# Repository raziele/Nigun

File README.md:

## Nigun (Melody)
RF down-converter for (but not only for) SDR

## PURPOSE
Allow low-frequency SDR (mainly RTL-SDR) to recieve wireless signals in frequencies higher than 1500MHz
Nigun is platform-independant, so it can be paired with other devices such as YARD stick ONE and PandwaRF too!

## MAIN PROPERTIES
* Dynamic LO - LO will be determined by the user and programmed by the MCU
* Almost no filtering - will leave this challenge outside of this project scope
* Power up and programming via micro-usb connector. Should be able to power up from a USB power-pack (but probably not from a computer port)
* Highest RF frequency will be 3GHz
* Product also features a VCO for signal-generation purposes. VCO support should be 200-2700MHz

## DESIGN DETAILS
Can be found currently on http://slides.com/raziele/software-define-radio-4-5-6-7-8#/
All details should be updated here in the near future

## CURRENT STATUS
2017-05: Finished PCB design. Working on some finishing but I should order first batch during June

## CREDITS
* All those who were patient enough to teach, review, and answer my endless questions
* Michele Perla and his HACK project - for the Atmel SAMD21E reference design

## LICENSE
I haven't dealt with the licensing part yet, though it will probably be under CERN OHL v. 1.2.
For now, please contact me for any licensing request.

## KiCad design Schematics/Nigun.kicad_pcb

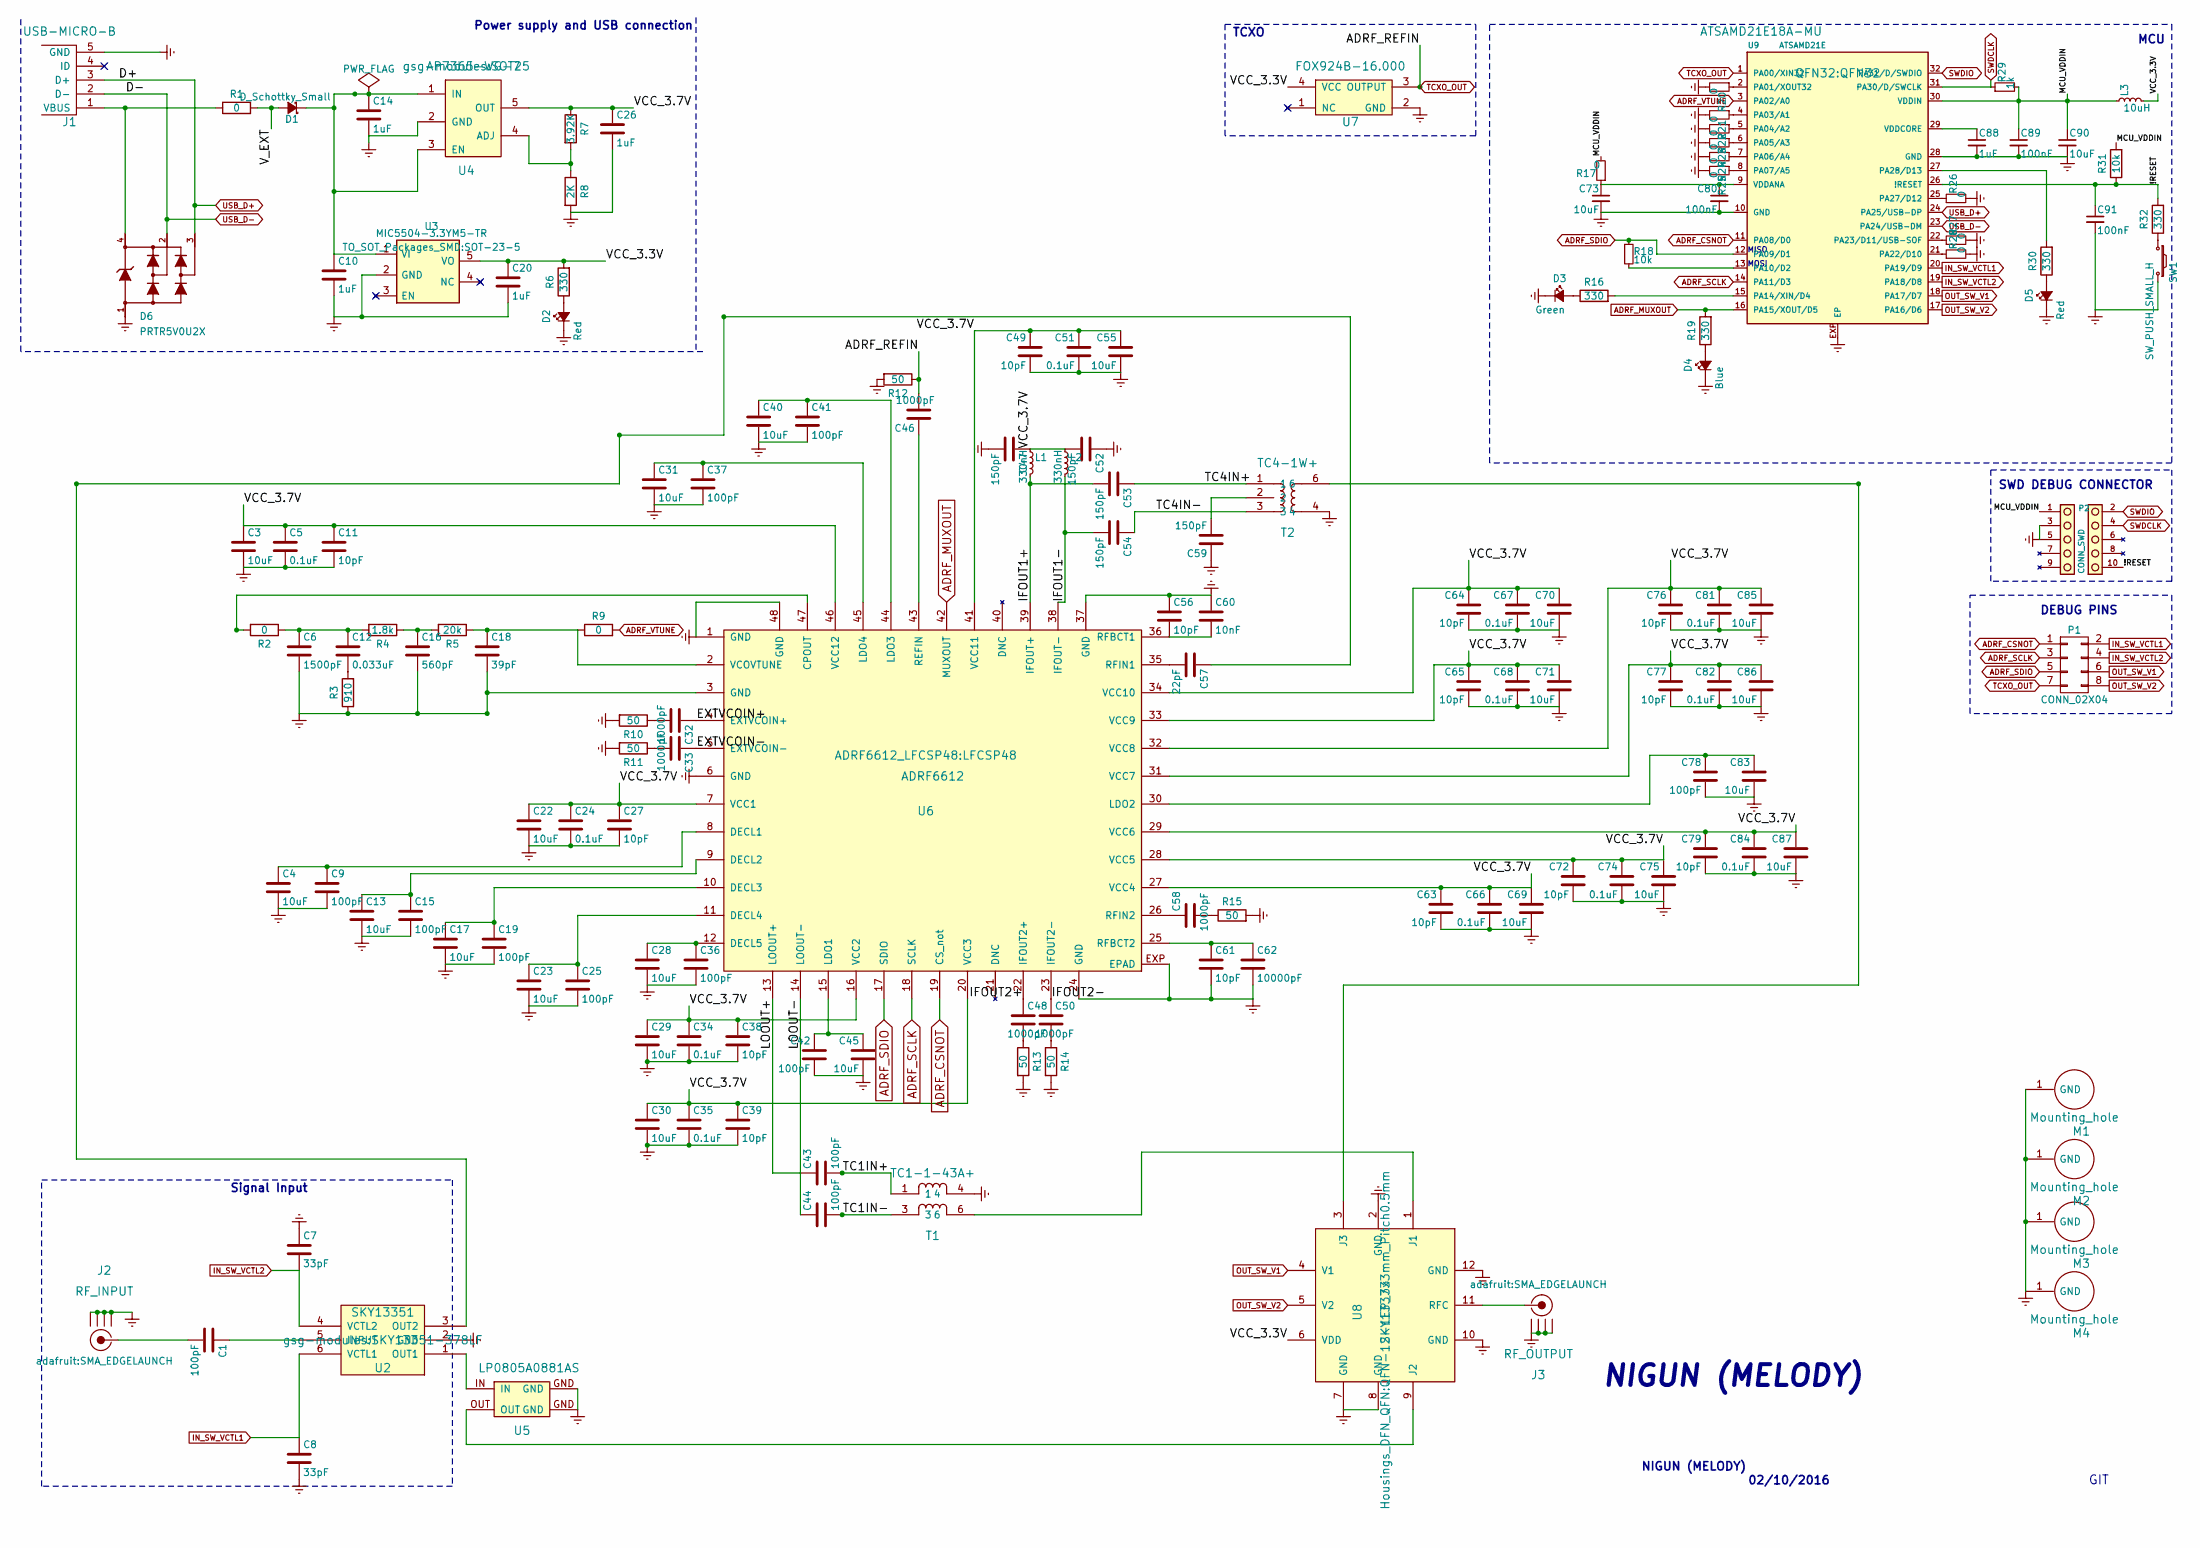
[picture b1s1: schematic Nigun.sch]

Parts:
C1, C9, C15, C19, C25, C36, C37, C41, C42, C43, C44, C78: 100pF; C_0402
C3, C4, C13, C17, C22, C23, C28, C29, C30, C31, C40, C45, C55, C69, C70, C71, C73, C75, C83, C85, C86, C87, C90: 10uF; C_0402
C5, C24, C34, C35, C51, C66, C67, C68, C74, C81, C82, C84: 0.1uF; C_0402
C6: 1500pF; C_0402
C7, C8: 33pF; C_0402
C10, C14, C20, C26, C88: 1uF; C_0402
C11, C27, C38, C39, C49, C56, C61, C63, C64, C65, C72, C76, C77, C79: 10pF; C_0402
C12: 0.033uF; C_0402
C16: 560pF; C_0402
C18: 39pF; C_0402
C32, C33, C46, C48, C50, C58: 1000pF; C_0402
C47, C52, C53, C54, C59: 150pF; C_0402
C57: 22pF; C_0402
C60: 10nF; C_0402
C62: 10000pF; C_0402
C80, C89, C91: 100nF; C_0402
D1: D_Schottky_Small; DO-214AA-SMB
D2, D5: Red; LED_kingsbright
D3: Green; LED_kingsbright
D4: Blue; LED_kingsbright
D6: PRTR5V0U2X; SOT143B
J1: USB-MICRO-B; FRAMATOME_10118194-0001LF
J2: RF_INPUT; SMA_EDGELAUNCH
J3: RF_OUTPUT; SMA_EDGELAUNCH
L1, L2: 330nH; C_0402
L3: 10uH; C_0603_HandSoldering
M1, M2, M3, M4: Mounting_hole; Mounting_hole_100mil
P1: CONN_02X04; HEADER-2x4
P2: CONN_SWD; HEADER-2x5
R1, R2, R9, R17, R20, R21, R22, R23, R24, R25, R26, R27, R28: 0; R_0402
R3: 910; R_0402
R4: 1.8k; R_0402
R5: 20k; R_0402
R6, R16, R19, R30, R32: 330; R_0402
R7: 3.92K; R_0402
R8: 2K; R_0402
R10, R11, R12, R13, R14, R15: 50; R_0402
R18, R31: 10k; R_0402
R29: 1k; R_0402
SW1: SW_PUSH_SMALL_H; Tactile_SW
T1: TC1-1-43A+; AT224-1A
T2: TC4-1W+; AT224-1A
U2: SKY13351; SKY13351-378LF
U3: MIC5504-3.3YM5-TR; SOT-23-5
U4: AP7365-WG-7; SOT25
U5: LP0805A0881AS; CP_0805
U6: ADRF6612; LFCSP48
U7: FOX924B-16.000; FOX924
U8: SKY13373; QFN-12-1EP_3x3mm_Pitch0.5mm
U9: ATSAMD21E; QFN32

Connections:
/!RESET: C91.1, P2.10 (nRESET), R31.1, R32.2, U9.26 (!RESET)
/EXTVCOIN+: C32.1, U6.4 (EXTVCOIN+)
/EXTVCOIN-: C33.1, U6.5 (EXTVCOIN-)
/IFOUT1+: C53.2, L1.2, U6.39 (IFOUT+)
/IFOUT1-: C54.2, L2.2, U6.38 (IFOUT-)
/IFOUT2+: C48.1, U6.22 (IFOUT2+)
/IFOUT2-: C50.1, U6.23 (IFOUT2-)
/LOOUT+: C43.1, U6.13 (LOOUT+)
/LOOUT-: C44.1, U6.14 (LOOUT-)
/MCU_VDDIN: C89.1, C90.1, L3.1, P2.1 (VTref), R17.2, R29.2, R31.2, U9.30 (VDDIN)
/TC1IN+: C43.2, T1.1
/TC1IN-: C44.2, T1.3
/TC4IN+: C53.1, T2.1
/TC4IN-: C54.1, T2.3
/VCC_3.3V: C20.1, L3.2, R6.2, U3.5 (VO), U7.4 (VCC), U8.6 (VDD)
/VCC_3.7V: C3.1, C5.1, C11.1, C22.1, C24.1, C26.1, C27.1, C29.1, C30.1, C34.1, C35.1, C38.1, C39.1, C47.1, C49.1, C51.1, C52.2, C55.1, C63.1, C64.1, C65.1, C66.1, C67.1, C68.1, C69.1, C70.1, C71.1, C72.1, C74.1, C75.1, C76.1, C77.1, C79.1, C81.1, C82.1, C84.1, C85.1, C86.1, C87.1, L1.1, L2.1, R7.1, U4.5 (OUT), U6.7 (VCC1), U6.16 (VCC2), U6.20 (VCC3), U6.27 (VCC4), U6.28 (VCC5), U6.29 (VCC6), U6.31 (VCC7), U6.32 (VCC8), U6.33 (VCC9), U6.34 (VCC10), U6.41 (VCC11), U6.46 (VCC12)
/V_EXT: D1.2 (A), R1.2
ADRF_CSNOT: P1.1, U6.19 (CS_not), U9.11 (PA08/D0)
ADRF_MUXOUT: R19.2, U6.42 (MUXOUT), U9.16 (PA15/XOUT/D5)
ADRF_SCLK: P1.3, U6.18 (SCLK), U9.14 (PA11/D3)
ADRF_SDIO: P1.5, R18.1, U6.17 (SDIO), U9.12 (PA09/D1)
ADRF_VTUNE: R9.2, U9.3 (PA02/A0)
Earth: C3.2, C4.2, C5.2, C6.2, C7.1, C8.2, C9.2, C10.2, C11.2, C13.2, C14.2, C15.2, C16.2, C17.2, C18.2, C19.2, C20.2, C22.2, C23.2, C24.2, C25.2, C26.2, C27.2, C28.2, C29.2, C30.2, C31.2, C34.2, C35.2, C36.2, C37.2, C38.2, C39.2, C40.2, C41.2, C42.2, C45.2, C47.2, C49.2, C51.2, C52.1, C55.2, C56.1, C59.1, C60.1, C61.2, C62.2, C63.2, C64.2, C65.2, C66.2, C67.2, C68.2, C69.2, C70.2, C71.2, C72.2, C73.2, C74.2, C75.2, C76.2, C77.2, C78.2, C79.2, C80.2, C81.2, C82.2, C83.2, C84.2, C85.2, C86.2, C87.2, C88.2, C89.2, C90.2, C91.2, D2.1 (K), D3.1 (K), D4.1 (K), D5.1 (K), D6.1, J1.5 (GND), J2.GND@ (GND1), J3.GND@ (GND1), M1.1, M2.1, M3.1, M4.1, P2.3 (GND), P2.5 (GND), R3.1, R8.2, R10.2, R11.2, R12.2, R13.2, R14.2, R15.2, R20.2, R21.2, R22.2, R23.2, R24.2, R25.2, R26.2, R27.2, R28.2, SW1.2, T1.4, T2.4, U2.2 (GND), U3.2 (GND), U4.2 (GND), U5.GND, U6.1 (GND), U6.3 (GND), U6.6 (GND), U6.24 (GND), U6.37 (GND), U6.48 (GND), U6.EXP (EPAD), U7.2 (GND), U8.2 (GND), U8.7 (GND), U8.8 (GND), U8.10 (GND), U8.12 (GND), U9.10 (GND), U9.28 (GND), U9.EXP (EP)
IN_SW_VCTL1: C8.1, P1.2, U2.6 (VCTL1), U9.20 (PA19/D9)
IN_SW_VCTL2: C7.2, P1.4, U2.4 (VCTL2), U9.19 (PA18/D8)
unnamed: C1.1, U2.5 (INPUT)
unnamed: C1.2, J2.P (RF)
unnamed: C4.1, C9.1, U6.8 (DECL1)
unnamed: C10.1, C14.1, D1.1 (C), U3.1 (VI), U4.1 (IN), U4.3 (EN)
unnamed: C6.1, C12.1, R2.1, R4.2
unnamed: C12.2, R3.2
unnamed: C13.1, C15.1, U6.9 (DECL2)
unnamed: C16.1, R4.1, R5.2
unnamed: C17.1, C19.1, U6.10 (DECL3)
unnamed: C18.1, R5.1, R9.1, U6.2 (VCOVTUNE)
unnamed: C23.1, C25.1, U6.11 (DECL4)
unnamed: C28.1, C36.1, U6.12 (DECL5)
unnamed: C31.1, C37.1, U6.45 (LDO4)
unnamed: C32.2, R10.1
unnamed: C33.2, R11.1
unnamed: C40.1, C41.1, U6.44 (LDO3)
unnamed: C42.1, C45.1, U6.15 (LDO1)
unnamed: C46.1, U6.43 (REFIN)
unnamed: C48.2, R13.1
unnamed: C50.2, R14.1
unnamed: C56.2, C60.2, U6.36 (RFBCT1)
unnamed: C57.1, U2.3 (OUT2)
unnamed: C57.2, U6.35 (RFIN1)
unnamed: C58.1, U6.26 (RFIN2)
unnamed: C58.2, R15.1
unnamed: C59.2, T2.2
unnamed: C61.1, C62.1, U6.25 (RFBCT2)
unnamed: C73.1, C80.1, R17.1, U9.9 (VDDANA)
unnamed: C78.1, C83.1, U6.30 (LDO2)
unnamed: C88.1, U9.29 (VDDCORE)
unnamed: D2.2 (A), R6.1
unnamed: D3.2 (A), R16.1
unnamed: D4.2 (A), R19.1
unnamed: D5.2 (A), R30.1
unnamed: D6.4, J1.1 (VBUS), R1.1
unnamed: J3.P (RF), U8.11 (RFC)
unnamed: R2.2, U6.47 (CPOUT)
unnamed: R7.2, R8.1, U4.4 (ADJ)
unnamed: R16.2, U9.15 (PA14/XIN/D4)
unnamed: R18.2, U9.13 (PA10/D2)
unnamed: R20.1, U9.2 (PA01/XOUT32)
unnamed: R21.1, U9.4 (PA03/A1)
unnamed: R22.1, U9.5 (PA04/A2)
unnamed: R23.1, U9.6 (PA05/A3)
unnamed: R24.1, U9.7 (PA06/A4)
unnamed: R25.1, U9.8 (PA07/A5)
unnamed: R26.1, U9.25 (PA27/D12)
unnamed: R27.1, U9.22 (PA23/D11/USB-SOF)
unnamed: R28.1, U9.21 (PA22/D10)
unnamed: R30.2, U9.27 (PA28/D13)
unnamed: R32.1, SW1.1
unnamed: T1.6, U8.1 (J1)
unnamed: T2.6, U8.3 (J3)
unnamed: U2.1 (OUT1), U5.IN
unnamed: U5.OUT, U8.9 (J2)
OUT_SW_V1: P1.6, U8.4 (V1), U9.18 (PA17/D7)
OUT_SW_V2: P1.8, U8.5 (V2), U9.17 (PA16/D6)
SWDCLK: P2.4 (SWDCLK), R29.1, U9.31 (PA30/D/SWCLK)
SWDIO: P2.2 (SWDIO), U9.32 (PA31/D/SWDIO)
TCXO_OUT: C46.2, P1.7, R12.1, U7.3 (OUTPUT), U9.1 (PA00/XIN32)
USB_D+: D6.3, J1.3 (D+), U9.24 (PA25/USB-DP)
USB_D-: D6.2, J1.2 (D-), U9.23 (PA24/USB-DM)

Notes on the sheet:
NIGUN (MELODY)
02/10/2016
GIT
Power supply and USB connection
Signal Input
MCU
MOSI
MISO
TCXO
SWD DEBUG CONNECTOR
DEBUG PINS

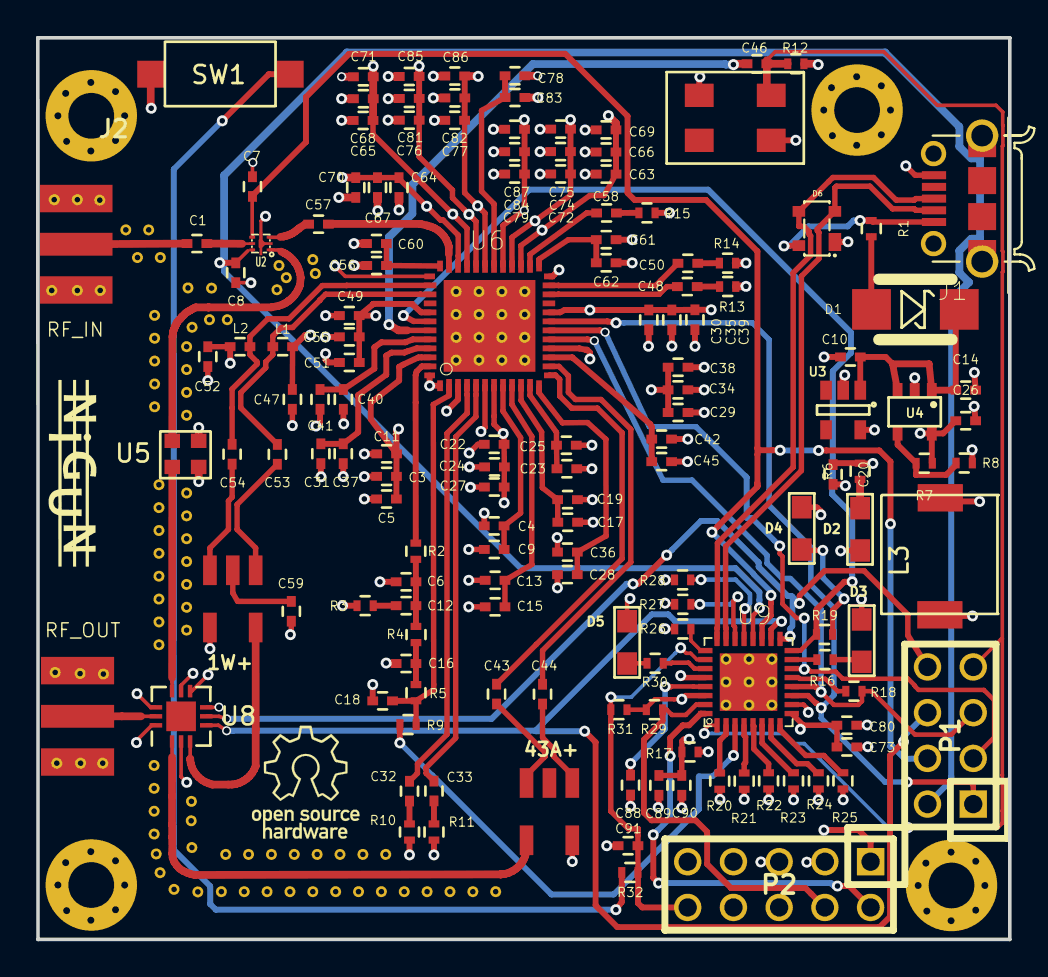
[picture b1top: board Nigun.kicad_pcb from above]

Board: 4 copper layers, 54.0 x 50.1 mm, 151 parts (0 on the bottom side), 87 nets.

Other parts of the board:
LOGO1: OSHW; OSHW-LOGO

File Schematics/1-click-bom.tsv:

References	Qty	Description
C1, C43, C44, C9, C15, C19, C25, C36, C41, C37, C78, C42	12	C 100pF Unpolarized capacitor 0402
C6	1	C 1500pF Unpolarized capacitor 0402
C8, C7	2	C 33pF Unpolarized capacitor 0402
C10, C20, C14, C26, C88	5	C 1uF Unpolarized capacitor 0402
C12	1	C 0.033uF Unpolarized capacitor 0402
C16	1	C 560pF Unpolarized capacitor 0402
C18	1	C 39pF Unpolarized capacitor 0402
C46, C58, C50, C48, C33, C32	6	C 1000pF Unpolarized capacitor 0402
C53, C54, C59, C52, C47	5	C 150pF Unpolarized capacitor 0402
C57	1	C 22pF Unpolarized capacitor 0402
C60	1	C 10nF Unpolarized capacitor 0402
C61, C63, C72, C79, C77, C56, C27, C38, C39, C76, C65, C64, C11, C49	14	C 10pF Unpolarized capacitor 0402
C62	1	C 10000pF Unpolarized capacitor 0402
C66, C74, C84, C82, C24, C34, C35, C81, C68, C67, C5, C51	12	C 0.1uF Unpolarized capacitor 0402
C69, C75, C87, C86, C29, C30, C85, C71, C70, C22, C4, C13, C17, C23, C28, C3, C40, C31, C55, C83, C45, C90, C73	23	C 10uF Unpolarized capacitor 0402
C89, C80, C91	3	C Small 100nF Unpolarized capacitor 0402
D1	1	D Schottky Small-RESCUE-Nigun Small DO-214AA-SMB
D3	1	Led Small-RESCUE-Nigun Green LED kingsbright
D4	1	Led Small-RESCUE-Nigun Blue LED kingsbright
D5, D2	2	Led Small-RESCUE-Nigun Red LED kingsbright
D6	1	PRTR5V0U2X SOT143B
J1	1	USB-MICRO-B FRAMATOME 10118194-0001LF
J2	1	SMA RF INPUT EDGELAUNCH
J3	1	SMA RF OUTPUT EDGELAUNCH
L1, L2	2	L Small 330nH Inductor, small symbol C 0402
L3	1	L Small 10uH Inductor, small symbol C 0603 HandSoldering
M1, M2, M3, M4	4	Mounting hole 100mil
P1	1	CONN 02X04 Connector, double row, 02x04 HEADER-2x4
P2	1	CONN SWD HEADER-2x5
R2, R9, R21, R22, R24, R23, R25, R1, R26, R27, R28, R20, R17	13	R 0 Resistor 0402
R3	1	R 910 Resistor 0402
R4	1	R 1.8k Resistor 0402
R5	1	R 20k Resistor 0402
R7	1	R 3.92K Resistor 0402
R8	1	R 2K Resistor 0402
R12, R15, R14, R13, R11, R10	6	R 50 Resistor 0402
R18, R31	2	R Small 10k Resistor, small symbol 0402
R19, R32, R30, R16, R6	5	R 330 Resistor 0402
R29	1	R Small 1k Resistor, small symbol 0402
SW1	1	SW PUSH SMALL H Tactile
T1	1	TC1-1-43A+ AT224-1A
T2	1	TC4-1W+ AT224-1A
U2	1	SKY13351 SKY13351-378LF
U3	1	MIC5504-3.3YM5-TR 300[mA] Fixed Low Drop Positive Voltage Regulator, Output 3.3V, SOT223 SOT-23-5
U4	1	AP7365-WG-7 SOT25
U5	1	LP0805A1119AS LP0805A0881AS CP 0805
U6	1	ADRF6612 Wideband Mixer and VCO LFCSP48
U7	1	FOX924B-16.000 FOX924
U8	1	SKY13373 QFN-12-1EP 3x3mm Pitch0.5mm
U9	1	ATSAMD21E Atmel SAM D21 Cortex M0+ series QFN32

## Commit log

2016-07-22 Updated some info about potential components
2016-09-09 Added spur calcs
2016-09-25 Adding main components datasheets and starting schematics
2016-10-02 - Updated schematics - Added mini-circuits TC1-1-43A+ transformer to kicad library - Added AVX low-pass filter to lkicad ibrary
2016-12-03 Schematics
2016-12-11 Schematics update
2016-12-27 Almost finished schematics, based on ATSAMD20E MCU
2017-01-15 Finished schematics
2017-01-21 replaced 45deg bent RF traces with curvy traces
2017-01-29 PCB design update - finished RF traces and 2 sides of 6612
2017-02-12 Changed ESD protection IC for USB bus
2017-02-24 Place and route updates
2017-03-06 Finished front layer
2017-03-12 added large inductor at the MCU powe input
2017-05-09 Finished PCB editing, first version of gerber files
2017-05-13 Added 3d model, updated components and readme
2017-05-16 Design update
2017-05-16 Switched order of VCC and GND layers
2017-05-17 Via size update and rearrange
2017-12-06 Finalized design for first prototype
